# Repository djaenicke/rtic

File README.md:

<p align="center">
  <h1 align="center">RTIC</h1>
</p>

### The Hardware
The Real Time Interface and Controller (RTIC) is a universal board for low-level robotics control and monitoring. The board can be ordered from [JLCPCB](https://jlcpcb.com/) using the [assembly](pcb/kicad/v2/assembly) and [gerber](pcb/kicad/v2/gerber) files.

#### Key Features
- 4 permanent magnet DC motor outputs
- 4 quadrature encoder inputs
- 6-axis IMU
- NRF24L01 socket for wireless communications
- USB (supports DFU via jumper)
- CAN breakout header

A [compatible 4-wheeled mobile robot base](https://www.amazon.com/Moebius-Mecanum-Platform-Omni-direactional-Raspberry/dp/B083XS2SD7) can be purchased directly from Amazon. :robot:

### Tools Setup ✔️
At a minium you will need the ARM GNU GCC Toolchain, Make and CMake to compile the source and generate executable artifacts.
-   [ARM GNU GCC Toolchain - 10-2020-q4-major](https://developer.arm.com/tools-and-software/open-source-software/developer-tools/gnu-toolchain/gnu-rm/downloads) - Other versions can be used but the current source is actively developed and tested using the 10-2020-q4-major release
-   Make -  Make is shipped with Linux and should already be present on the developers system. If the developer is running Windows they can either use WSL to run a Linux instance or install Make on Windows via [MinGW](https://sourceforge.net/projects/mingw/)
-   [CMake](https://cmake.org/download/)

To flash and debug the target this project uses a couple of different tools. PyOCD, Segger JLink, or STLINK can be used as the programming/debugging medium, and a VScode extension called Cortex-Debug gives a user interface within VScode for stepping through the source, settings breakpoints and viewing registers/variables within the target.
-   [PyOCD](https://github.com/pyocd/pyOCD#installing)
-   [JLink](https://www.segger.com/downloads/jlink/)
-   [STLINK](https://github.com/stlink-org/stlink)
-   [VScode](https://code.visualstudio.com/)
-   [ARM Developer Extension Pack for VScode](https://marketplace.visualstudio.com/items?itemName=Glasslabs.arm-developer-toolkit)

As an alternative to the debuggging tools, dfu-util can be used to program the board using the built in DFU capability of the bootloader.
-   [dfu-util](https://manpages.ubuntu.com/manpages/xenial/man1/dfu-util.1.html)
    - Linux - ```sudo apt-get install dfu-util```

***NOTE: After installing your desired debug toolset, please ensure the chosen application is accessible from the command line (pyocd or JLinkExe)***

To format all source files, you will need to install Clang-Format.
-   [Clang-Format](https://clang.llvm.org/docs/ClangFormat.html)
    - Linux - ```sudo apt-get install clang-format```

### Compiling, Flashing & Testing ✨
After a fresh clone, the ```setup``` scripts can be used to initialize the project. Passing ```release``` as an argument will generate a release build. Otherwise a ```debug``` build is generated.
##### Windows
```console
setup.ps1
```
##### Linux
```console
./setup.sh
```

Once a project has been initialized, the following commands should be ran from the ```build/``` folder

To clean the working directory:
```console
make clean
```

To compile the source:
```console
make -j8
```

To erase the connected target with PyOCD or Segger JLink:
```console
make erase
```

To flash the connected target with PyOCD or Segger JLink:
```console
make flash
```

To flash the connected target via DFU:
```console
make dfu
```

To execute unit tests:
```console
make test
```

To format source files:
```console
make format
```

### Source Documentation Style 📃
Read more about the Source documentation style [here](./doc/DOCUMENTATION_STYLE.md)

### Develop Strategy 📖
Read more about the Git develop strategy used [here](./doc/DEVELOP_STRATEGY.md)

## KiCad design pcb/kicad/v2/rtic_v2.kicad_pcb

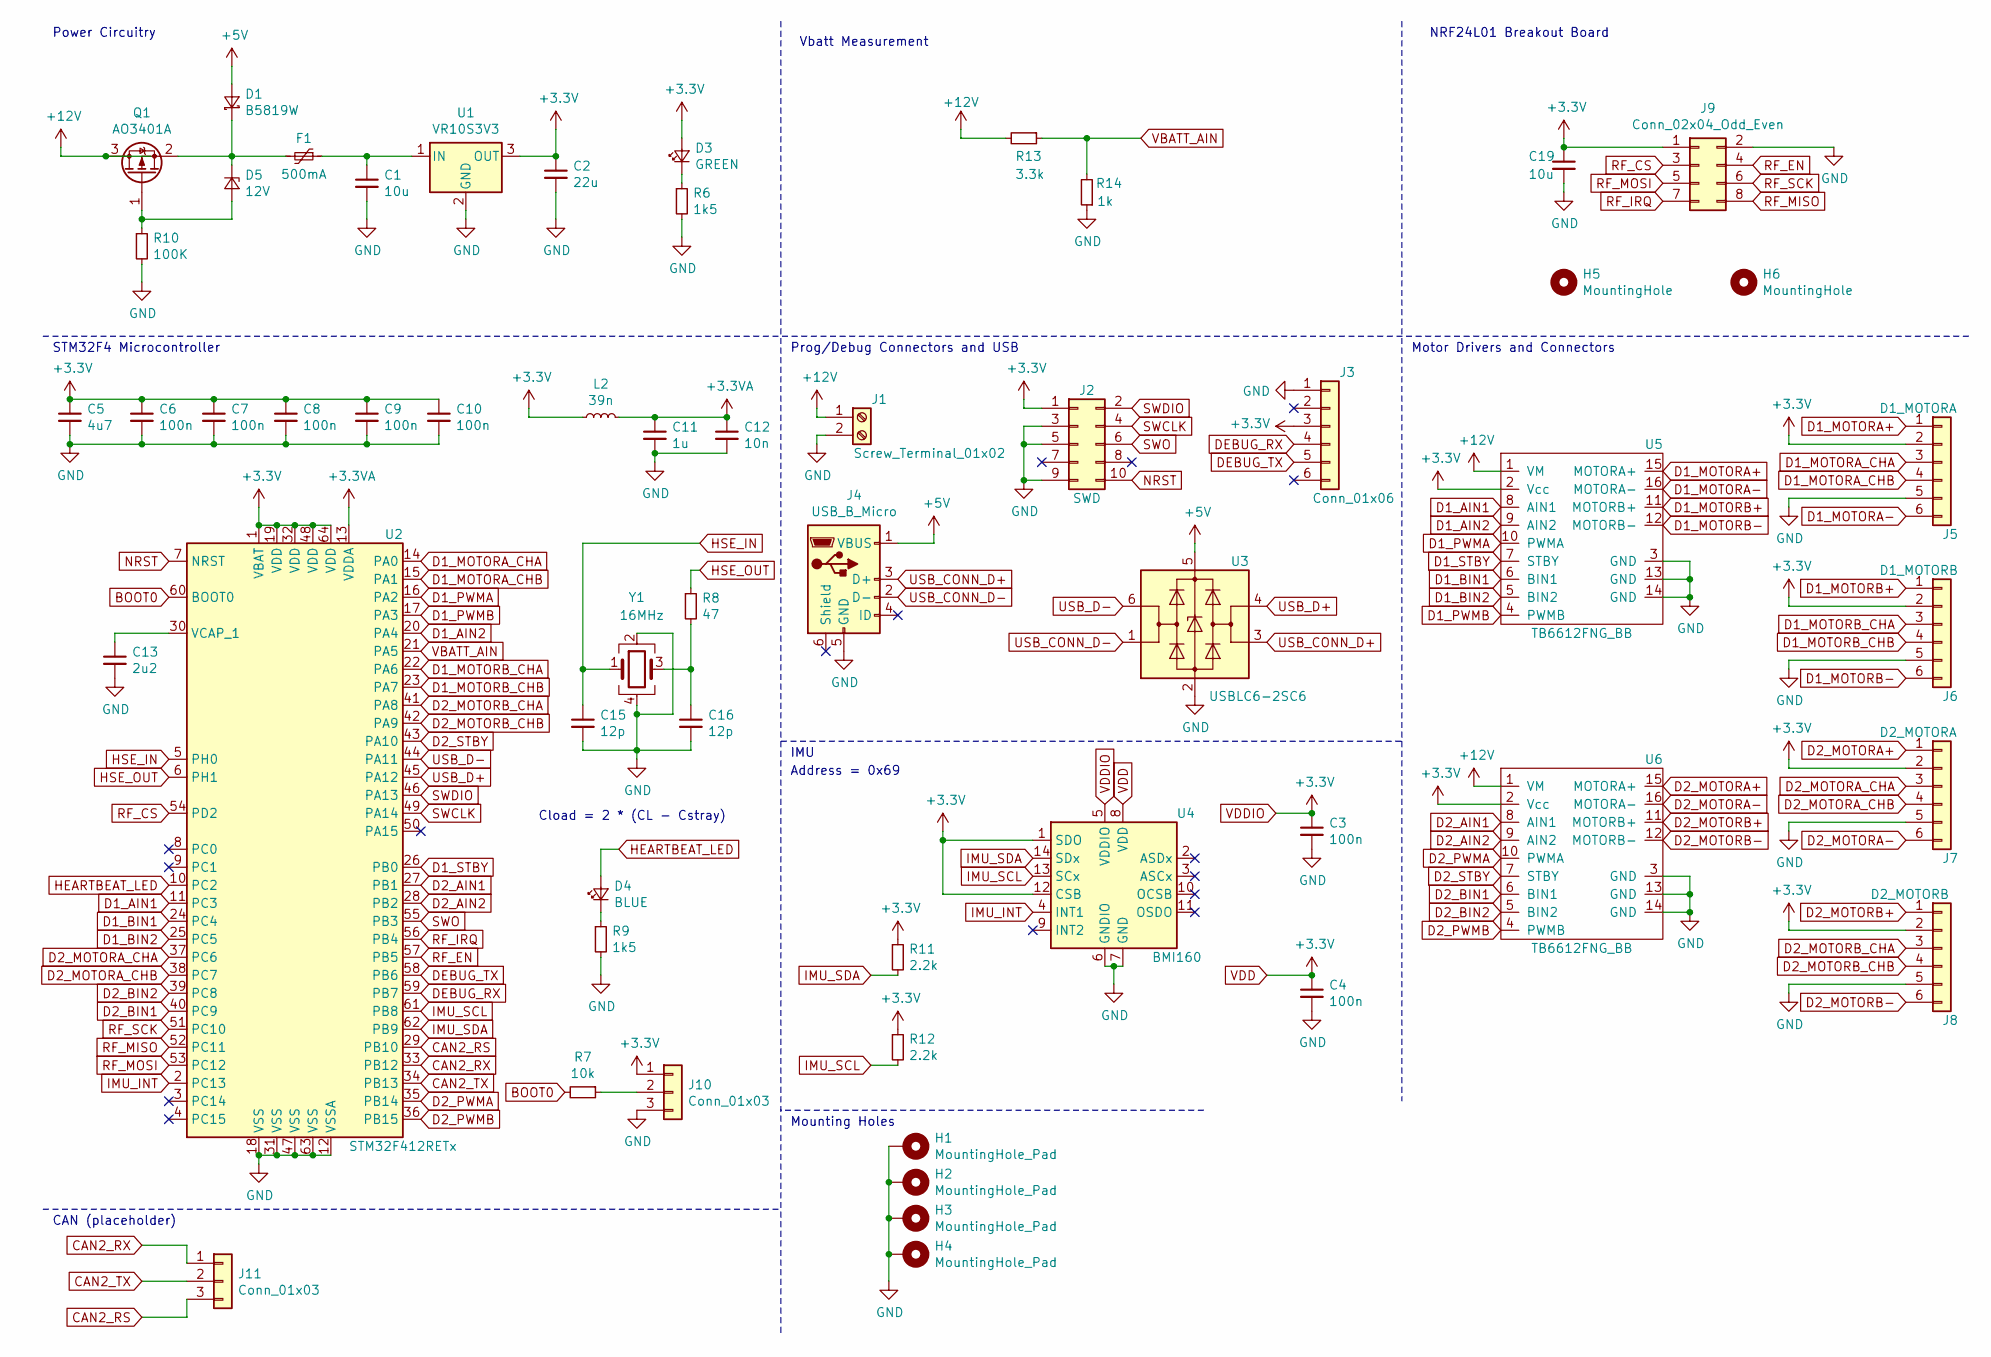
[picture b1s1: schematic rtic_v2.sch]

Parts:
C1, C19: 10u; C_1206_3216Metric; LCSC Part # C13585
C2: 22u; C_1206_3216Metric; LCSC Part # C12891
C3, C4, C6, C7, C8, C9, C10: 100n; C_0402_1005Metric; LCSC Part # C1525
C5: 4u7; C_0603_1608Metric; LCSC Part # C19666
C11: 1u; C_0603_1608Metric; LCSC Part # C15849
C12: 10n; C_0402_1005Metric; LCSC Part # C15195
C13: 2u2; C_0603_1608Metric; LCSC Part # C23630
C15, C16: 12p; C_0402_1005Metric; LCSC Part # C1547
D1: B5819W; D_SOD-123; LCSC Part # C8598
D3: GREEN; LED_0603_1608Metric; LCSC Part # C72043
D4: BLUE; LED_0603_1608Metric; LCSC Part # C72041
D5: 12V; D_SOD-323; LCSC Part # C261261
F1: 500mA; Fuse_1206_3216Metric; LCSC Part # C99561
H1, H2, H3, H4: MountingHole_Pad; MountingHole_3.2mm_M3_Pad_Via
H5, H6: MountingHole; MountingHole_2.7mm_M2.5
J1: Screw_Terminal_01x02; TerminalBlock_Phoenix_PT-1,5-2-5.0-H_1x02_P5.00mm_Horizontal
J2: SWD; PinHeader_2x05_P1.27mm_Vertical_SMD
J3: Conn_01x06; PinHeader_1x06_P2.54mm_Vertical
J4: USB_B_Micro; USB_Micro-B_Amphenol_10103594-0001LF_Horizontal
J5: D1_MOTORA; JST_PH_B6B-PH-K_1x06_P2.00mm_Vertical
J6: D1_MOTORB; JST_PH_B6B-PH-K_1x06_P2.00mm_Vertical
J7: D2_MOTORA; JST_PH_B6B-PH-K_1x06_P2.00mm_Vertical
J8: D2_MOTORB; JST_PH_B6B-PH-K_1x06_P2.00mm_Vertical
J9: Conn_02x04_Odd_Even; PinSocket_2x04_P2.54mm_Vertical
J10, J11: Conn_01x03; PinHeader_1x03_P2.54mm_Vertical
L2: 39n; L_0402_1005Metric; LCSC Part # C26443
Q1: AO3401A; SOT-23; LCSC Part # C15127
R6, R9: 1k5; R_0603_1608Metric; LCSC Part # C22843
R7: 10k; R_0402_1005Metric; LCSC Part # C25744
R8: 47; R_0402_1005Metric; LCSC Part # C25118
R10: 100K; R_0603_1608Metric; LCSC Part # C25803
R11, R12: 2.2k; R_0402_1005Metric; LCSC Part # C25879
R13: 3.3k; R_0402_1005Metric; LCSC Part # C25890
R14: 1k; R_0402_1005Metric; LCSC Part # C11702
U1: VR10S3V3
U2: STM32F412RETx; LQFP-64_10x10mm_P0.5mm; LCSC Part # C89374
U3: USBLC6-2SC6; SOT-23-6; LCSC Part # C7519
U4: BMI160; Bosch_LGA-14_3x2.5mm_P0.5mm; LCSC Part # C94021
U5, U6: TB6612FNG_BB
Y1: 16MHz; Crystal_SMD_3225-4Pin_3.2x2.5mm; LCSC Part # C13738

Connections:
+3.3VA: C11.1, C12.1, L2.2, U2.13 (VDDA)
+5V: D1.2 (A), J4.1 (VBUS), U3.5 (VBUS)
+12V: J1.1, Q1.3 (D), R13.2, U5.1 (VM), U6.1 (VM)
BOOT0: R7.2, U2.60 (BOOT0)
CAN2_RS: J11.3, U2.29 (PB10)
CAN2_RX: J11.1, U2.33 (PB12)
CAN2_TX: J11.2, U2.34 (PB13)
D1_AIN1: U2.11 (PC3), U5.8 (AIN1)
D1_AIN2: U2.20 (PA4), U5.9 (AIN2)
D1_BIN1: U2.24 (PC4), U5.6 (BIN1)
D1_BIN2: U2.25 (PC5), U5.5 (BIN2)
D1_MOTORA+: J5.1, U5.15 (MOTORA+)
D1_MOTORA-: J5.6, U5.16 (MOTORA-)
D1_MOTORA_CHA: J5.3, U2.14 (PA0)
D1_MOTORA_CHB: J5.4, U2.15 (PA1)
D1_MOTORB+: J6.1, U5.11 (MOTORB+)
D1_MOTORB-: J6.6, U5.12 (MOTORB-)
D1_MOTORB_CHA: J6.3, U2.22 (PA6)
D1_MOTORB_CHB: J6.4, U2.23 (PA7)
D1_PWMA: U2.16 (PA2), U5.10 (PWMA)
D1_PWMB: U2.17 (PA3), U5.4 (PWMB)
D1_STBY: U2.26 (PB0), U5.7 (STBY)
D2_AIN1: U2.27 (PB1), U6.8 (AIN1)
D2_AIN2: U2.28 (PB2), U6.9 (AIN2)
D2_BIN1: U2.40 (PC9), U6.6 (BIN1)
D2_BIN2: U2.39 (PC8), U6.5 (BIN2)
D2_MOTORA+: J7.1, U6.15 (MOTORA+)
D2_MOTORA-: J7.6, U6.16 (MOTORA-)
D2_MOTORA_CHA: J7.3, U2.37 (PC6)
D2_MOTORA_CHB: J7.4, U2.38 (PC7)
D2_MOTORB+: J8.1, U6.11 (MOTORB+)
D2_MOTORB-: J8.6, U6.12 (MOTORB-)
D2_MOTORB_CHA: J8.3, U2.41 (PA8)
D2_MOTORB_CHB: J8.4, U2.42 (PA9)
D2_PWMA: U2.35 (PB14), U6.10 (PWMA)
D2_PWMB: U2.36 (PB15), U6.4 (PWMB)
D2_STBY: U2.43 (PA10), U6.7 (STBY)
DEBUG_RX: J3.4, U2.59 (PB7)
DEBUG_TX: J3.5, U2.58 (PB6)
GND: C1.2, C2.2, C3.2, C4.2, C5.2, C6.2, C7.2, C8.2, C9.2, C10.2, C11.2, C12.2, C13.2, C15.2, C16.2, C19.2, H1.1, H2.1, H3.1, H4.1, J1.2, J2.3, J2.5, J2.9, J3.1, J4.5 (GND), J5.5, J6.5, J7.5, J8.5, J9.2, J10.3, R6.2, R9.2, R10.2, R14.1, U1.2 (GND), U2.12 (VSSA), U2.18 (VSS), U2.31 (VSS), U2.47 (VSS), U2.63 (VSS), U3.2 (GND), U4.6 (GNDIO), U4.7 (GND), U5.3 (GND), U5.13 (GND), U5.14 (GND), U6.3 (GND), U6.13 (GND), U6.14 (GND), Y1.2, Y1.4
HEARTBEAT_LED: D4.2 (A), U2.10 (PC2)
HSE_IN: C15.1, U2.5 (PH0), Y1.1
HSE_OUT: R8.1, U2.6 (PH1)
IMU_INT: U2.2 (PC13), U4.4 (INT1)
IMU_SCL: R12.2, U2.61 (PB8), U4.13 (SCx)
IMU_SDA: R11.2, U2.62 (PB9), U4.14 (SDx)
NRST: J2.10, U2.7 (NRST)
unnamed: C1.1, F1.1, U1.1 (IN)
unnamed: C13.1, U2.30 (VCAP_1)
unnamed: C16.1, R8.2, Y1.3
unnamed: D1.1 (K), D5.1 (K), F1.2, Q1.2 (S)
unnamed: D3.1 (K), R6.1
unnamed: D4.1 (K), R9.1
unnamed: D5.2 (A), Q1.1 (G), R10.1
unnamed: J10.2, R7.1
RF_CS: J9.3, U2.54 (PD2)
RF_EN: J9.4, U2.57 (PB5)
RF_IRQ: J9.7, U2.56 (PB4)
RF_MISO: J9.8, U2.52 (PC11)
RF_MOSI: J9.5, U2.53 (PC12)
RF_SCK: J9.6, U2.51 (PC10)
SWCLK: J2.4, U2.49 (PA14)
SWDIO: J2.2, U2.46 (PA13)
SWO: J2.6, U2.55 (PB3)
USB_CONN_D+: J4.3 (D+), U3.3 (I/O2)
USB_CONN_D-: J4.2 (D-), U3.1 (I/O1)
USB_D+: U2.45 (PA12), U3.4 (I/O2)
USB_D-: U2.44 (PA11), U3.6 (I/O1)
VBATT_AIN: R13.1, R14.2, U2.21 (PA5)
VDD: C2.1, C3.1, C4.1, C5.1, C6.1, C7.1, C8.1, C9.1, C10.1, C19.1, D3.2 (A), J2.1, J3.3, J5.2, J6.2, J7.2, J8.2, J9.1, J10.1, L2.1, R11.1, R12.1, U1.3 (OUT), U2.1 (VBAT), U2.19 (VDD), U2.32 (VDD), U2.48 (VDD), U2.64 (VDD), U4.1 (SDO), U4.5 (VDDIO), U4.8 (VDD), U4.12 (CSB), U5.2 (Vcc), U6.2 (Vcc)

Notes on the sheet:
Cload = 2 * (CL - Cstray)
STM32F4 Microcontroller
Power Circuitry
Prog/Debug Connectors and USB
IMU
Mounting Holes
Motor Drivers and Connectors
NRF24L01 Breakout Board
CAN (placeholder)
Vbatt Measurement
Address = 0x69

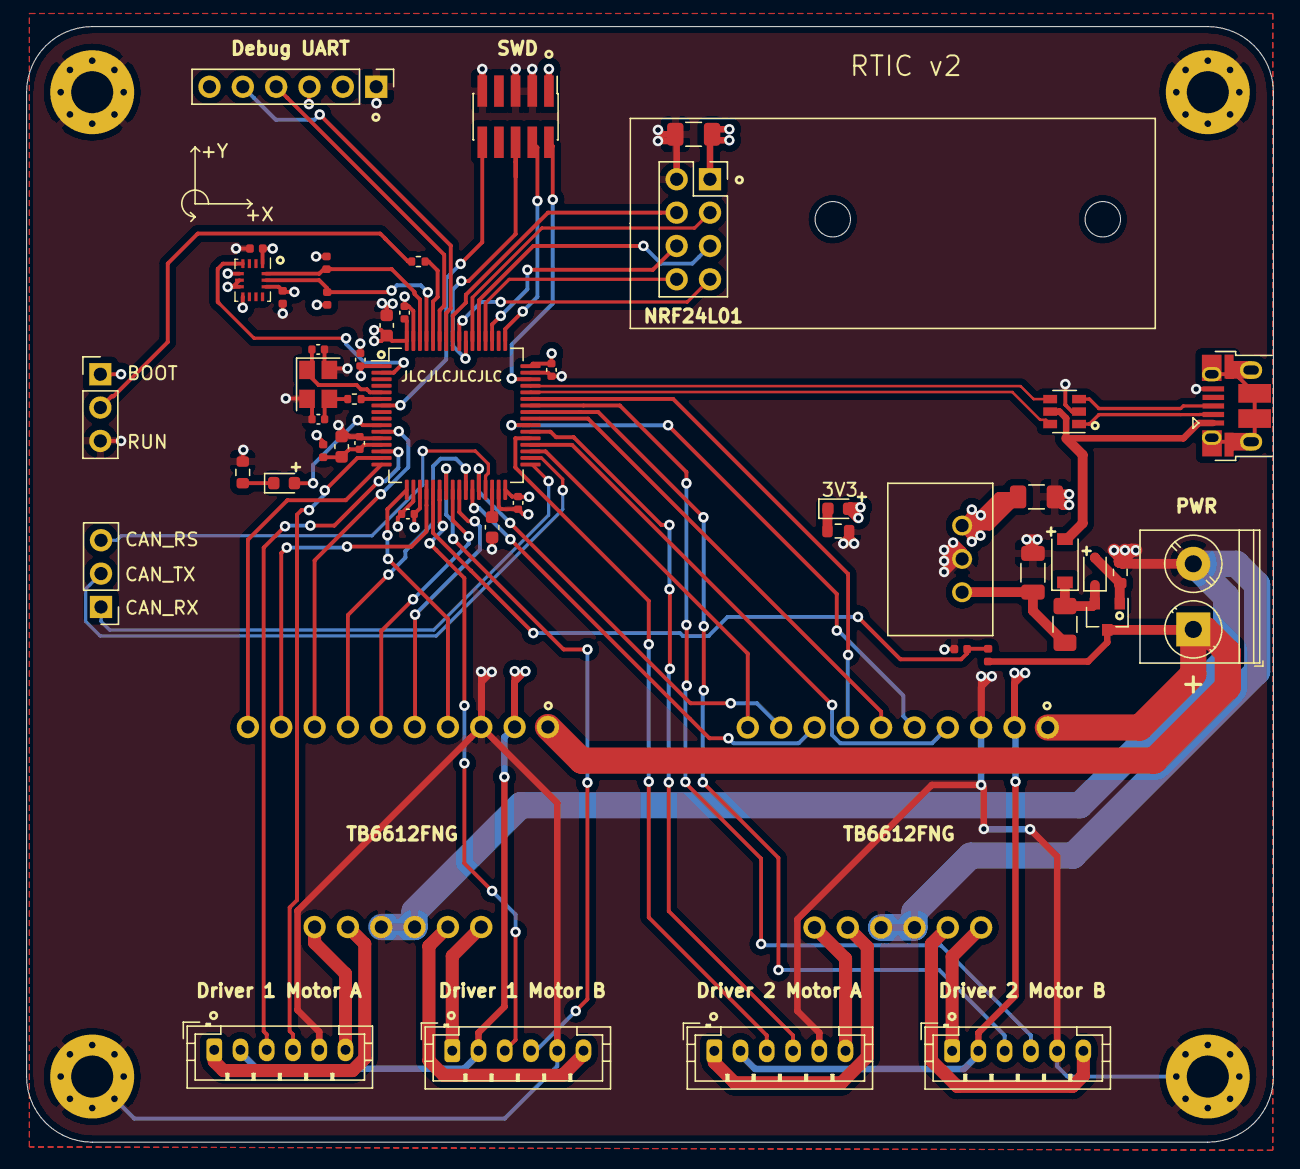
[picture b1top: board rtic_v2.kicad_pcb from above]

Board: 4 copper layers, 95.0 x 85.0 mm, 56 parts (0 on the bottom side), 70 nets.

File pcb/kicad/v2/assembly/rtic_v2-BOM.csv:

Comment,Designator,Footprint,LCSC
"10u","C1,C19","Capacitor_SMD:C_1206_3216Metric","C13585"
"1u","C11","Capacitor_SMD:C_0603_1608Metric","C15849"
"10n","C12","Capacitor_SMD:C_0402_1005Metric","C15195"
"2u2","C13","Capacitor_SMD:C_0603_1608Metric","C23630"
"12p","C15,C16","Capacitor_SMD:C_0402_1005Metric","C1547"
"22u","C2","Capacitor_SMD:C_1206_3216Metric","C12891"
"4u7","C5","Capacitor_SMD:C_0603_1608Metric","C19666"
"100n","C3,C4,C6,C7,C8,C9,C10","Capacitor_SMD:C_0402_1005Metric","C1525"
"B5819W","D1","Diode_SMD:D_SOD-123","C8598"
"GREEN","D3","LED_SMD:LED_0603_1608Metric","C72043"
"BLUE","D4","LED_SMD:LED_0603_1608Metric","C72041"
"12V","D5","Diode_SMD:D_SOD-323","C261261"
"500mA","F1","Fuse:Fuse_1206_3216Metric","C99561"
"MountingHole_Pad","H1,H2,H3,H4","MountingHole:MountingHole_3.2mm_M3_Pad_Via",""
"MountingHole","H5,H6","MountingHole:MountingHole_2.7mm_M2.5",""
"Screw_Terminal_01x02","J1","TerminalBlock_Phoenix:TerminalBlock_Phoenix_PT-1,5-2-5.0-H_1x02_P5.00mm_Horizontal",""
"Conn_01x03","J10,J11","Connector_PinHeader_2.54mm:PinHeader_1x03_P2.54mm_Vertical",""
"SWD","J2","Connector_PinHeader_1.27mm:PinHeader_2x05_P1.27mm_Vertical_SMD",""
"Conn_01x06","J3","Connector_PinHeader_2.54mm:PinHeader_1x06_P2.54mm_Vertical",""
"USB_B_Micro","J4","Connector_USB:USB_Micro-B_Amphenol_10103594-0001LF_Horizontal",""
"D1_MOTORA","J5","Connector_JST:JST_PH_B6B-PH-K_1x06_P2.00mm_Vertical",""
"D1_MOTORB","J6","Connector_JST:JST_PH_B6B-PH-K_1x06_P2.00mm_Vertical",""
"D2_MOTORA","J7","Connector_JST:JST_PH_B6B-PH-K_1x06_P2.00mm_Vertical",""
"D2_MOTORB","J8","Connector_JST:JST_PH_B6B-PH-K_1x06_P2.00mm_Vertical",""
"Conn_02x04_Odd_Even","J9","Connector_PinSocket_2.54mm:PinSocket_2x04_P2.54mm_Vertical",""
"39n","L2","Inductor_SMD:L_0402_1005Metric","C26443"
"AO3401A","Q1","Package_TO_SOT_SMD:SOT-23","C15127"
"100K","R10","Resistor_SMD:R_0603_1608Metric","C25803"
"2.2k","R11,R12","Resistor_SMD:R_0402_1005Metric","C25879"
"3.3k","R13","Resistor_SMD:R_0402_1005Metric","C25890"
"1k","R14","Resistor_SMD:R_0402_1005Metric","C11702"
"10k","R7","Resistor_SMD:R_0402_1005Metric","C25744"
"47","R8","Resistor_SMD:R_0402_1005Metric","C25118"
"1k5","R6,R9","Resistor_SMD:R_0603_1608Metric","C22843"
"VR10S3V3","U1","dj:VR10S3V3",""
"STM32F412RETx","U2","Package_QFP:LQFP-64_10x10mm_P0.5mm","C89374"
"USBLC6-2SC6","U3","Package_TO_SOT_SMD:SOT-23-6","C7519"
"BMI160","U4","Package_LGA:Bosch_LGA-14_3x2.5mm_P0.5mm","C94021"
"TB6612FNG_BB","U5,U6","dj:TB6612FNG_BB",""
"16MHz","Y1","Crystal:Crystal_SMD_3225-4Pin_3.2x2.5mm","C13738"

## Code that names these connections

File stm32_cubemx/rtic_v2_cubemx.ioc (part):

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Mcu.Name=STM32F412R(E-G)Tx
Mcu.Package=LQFP64
Mcu.UserName=STM32F412RETx
PA0.GPIOParameters=GPIO_Label
PA0.GPIO_Label=D1_MOTORA_CHA
PA0.Signal=S_TIM5_CH1
PA1.GPIOParameters=GPIO_Label
PA1.GPIO_Label=D1_MOTORA_CHB
PA1.Signal=S_TIM5_CH2
PA10.GPIOParameters=GPIO_Label
PA10.GPIO_Label=D2_STBY
PA10.Signal=GPIO_Output
PA11.Mode=Device_Only
PA11.Signal=USB_OTG_FS_DM
PA12.Mode=Device_Only
PA12.Signal=USB_OTG_FS_DP
PA13.Signal=SYS_JTMS-SWDIO
PA14.Signal=SYS_JTCK-SWCLK
PA2.GPIOParameters=GPIO_Label
PA2.GPIO_Label=D1_PWMA
PA2.Signal=S_TIM9_CH1
PA3.GPIOParameters=GPIO_Label
PA3.GPIO_Label=D1_PWMB
PA3.Signal=S_TIM9_CH2
PA4.GPIOParameters=GPIO_Label
PA4.GPIO_Label=D1_AIN2
PA4.Signal=GPIO_Output
PA5.GPIOParameters=GPIO_Label
PA5.GPIO_Label=VBATT_AIN
PA5.Signal=ADCx_IN5
PA6.GPIOParameters=GPIO_Label
PA6.GPIO_Label=D1_MOTORB_CHA
PA6.Signal=S_TIM3_CH1
PA7.GPIOParameters=GPIO_Label
PA7.GPIO_Label=D1_MOTORB_CHB
PA7.Signal=S_TIM3_CH2
PA8.GPIOParameters=GPIO_Label,GPIO_ModeDefaultEXTI
PA8.GPIO_Label=D2_MOTORB_CHA
PA8.GPIO_ModeDefaultEXTI=GPIO_MODE_IT_RISING_FALLING
PA8.Signal=GPXTI8
PA9.GPIOParameters=GPIO_Label,GPIO_ModeDefaultEXTI
PA9.GPIO_Label=D2_MOTORB_CHB
PA9.GPIO_ModeDefaultEXTI=GPIO_MODE_IT_RISING_FALLING
PA9.Signal=GPXTI9
PB0.GPIOParameters=GPIO_Label
PB0.GPIO_Label=D1_STBY
PB0.Signal=GPIO_Output
PB1.GPIOParameters=GPIO_Label
PB1.GPIO_Label=D2_AIN1
PB1.Signal=GPIO_Output
PB10.GPIOParameters=GPIO_Label
PB10.GPIO_Label=CAN2_RS
PB10.Signal=GPIO_Output
PB12.Mode=CAN_Activate
PB12.Signal=CAN2_RX
PB13.Mode=CAN_Activate
PB13.Signal=CAN2_TX
PB14.GPIOParameters=GPIO_Label
PB14.GPIO_Label=D2_PWMA
PB14.Signal=S_TIM12_CH1
PB15.GPIOParameters=GPIO_Label
PB15.GPIO_Label=D2_PWMB
PB15.Signal=S_TIM12_CH2
PB2.GPIOParameters=GPIO_Label
PB2.GPIO_Label=D2_AIN2
PB2.Signal=GPIO_Output
PB3.Signal=SYS_JTDO-SWO
PB4.GPIOParameters=GPIO_Label
PB4.GPIO_Label=RF_IRQ
PB4.Signal=GPIO_Input
PB5.GPIOParameters=GPIO_Label
PB5.GPIO_Label=RF_EN
PB5.Signal=GPIO_Output
PB6.GPIOParameters=GPIO_Label
PB6.GPIO_Label=DEBUG_TX
PB6.Mode=Asynchronous
PB6.Signal=USART1_TX
PB7.GPIOParameters=GPIO_Label
PB7.GPIO_Label=DEBUG_RX
PB7.Mode=Asynchronous
PB7.Signal=USART1_RX
PB8.GPIOParameters=GPIO_Label
PB8.GPIO_Label=IMU_SCL
PB8.Mode=I2C
PB8.Signal=I2C1_SCL
PB9.GPIOParameters=GPIO_Label
PB9.GPIO_Label=IMU_SDA
PB9.Mode=I2C
PB9.Signal=I2C1_SDA
PC10.GPIOParameters=GPIO_Label
PC10.GPIO_Label=RF_SCK
PC10.Mode=Full_Duplex_Master
PC10.Signal=SPI3_SCK
PC11.GPIOParameters=GPIO_Label
PC11.GPIO_Label=RF_MISO
PC11.Mode=Full_Duplex_Master
PC11.Signal=SPI3_MISO
PC12.GPIOParameters=GPIO_Label
PC12.GPIO_Label=RF_MOSI
PC12.Mode=Full_Duplex_Master
PC12.Signal=SPI3_MOSI
PC13.GPIOParameters=GPIO_Label
PC13.GPIO_Label=IMU_INT
PC13.Signal=GPIO_Input
PC14-OSC32_IN.Mode=LSE-External-Oscillator
PC14-OSC32_IN.Signal=RCC_OSC32_IN
PC15-OSC32_OUT.Mode=LSE-External-Oscillator
PC15-OSC32_OUT.Signal=RCC_OSC32_OUT
PC2.GPIOParameters=GPIO_Label
PC2.GPIO_Label=HEARTBEAT_LED
PC2.Signal=GPIO_Output
PC3.GPIOParameters=GPIO_Label
PC3.GPIO_Label=D1_AIN1
PC3.Signal=GPIO_Output
PC4.GPIOParameters=GPIO_Label
PC4.GPIO_Label=D1_BIN1
PC4.Signal=GPIO_Output
PC5.GPIOParameters=GPIO_Label
PC5.GPIO_Label=D1_BIN2
PC5.Signal=GPIO_Output
PC6.GPIOParameters=GPIO_Label,GPIO_ModeDefaultEXTI
PC6.GPIO_Label=D2_MOTORA_CHA
PC6.GPIO_ModeDefaultEXTI=GPIO_MODE_IT_RISING_FALLING
PC6.Signal=GPXTI6
PC7.GPIOParameters=GPIO_Label,GPIO_ModeDefaultEXTI
PC7.GPIO_Label=D2_MOTORA_CHB
PC7.GPIO_ModeDefaultEXTI=GPIO_MODE_IT_RISING_FALLING
PC7.Signal=GPXTI7
PC8.GPIOParameters=GPIO_Label
PC8.GPIO_Label=D2_BIN2
PC8.Signal=GPIO_Output
PC9.GPIOParameters=GPIO_Label
PC9.GPIO_Label=D2_BIN1
PC9.Signal=GPIO_Output
PD2.GPIOParameters=GPIO_Label
PD2.GPIO_Label=RF_CS
PD2.Signal=GPIO_Output
PH0\ -\ OSC_IN.GPIOParameters=GPIO_Label
PH0\ -\ OSC_IN.GPIO_Label=HSE_IN
PH0\ -\ OSC_IN.Mode=HSE-External-Oscillator
PH0\ -\ OSC_IN.Signal=RCC_OSC_IN
PH1\ -\ OSC_OUT.GPIOParameters=GPIO_Label
PH1\ -\ OSC_OUT.GPIO_Label=HSE_OUT
PH1\ -\ OSC_OUT.Mode=HSE-External-Oscillator
PH1\ -\ OSC_OUT.Signal=RCC_OSC_OUT
RCC.HSE_VALUE=16000000
RCC.SYSCLKFreq_VALUE=16000000
RCC.SYSCLKSource=RCC_SYSCLKSOURCE_HSE
board=custom

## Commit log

2022-04-02 added STM32F4xx HAL and set project specific CMake variables
2022-04-02 removed readme checklist
2022-04-02 moved firmware into separate directory
2022-04-03 initial implementation of board.c
2022-04-03 added format and dfu make targets
2022-04-03 fixed ci build
2022-04-03 moved doc directory to root and moved .clang-format into firmware directory
2022-04-03 added kicad, assembly, and gerber files
2022-04-03 added cubemx ioc for v2 pcb
2022-04-17 added the ability to use C++
2022-04-17 added GPIO class
2022-04-17 added DigitalIn and DigitalOut classes
2022-04-17 moved initBoard call into startup code
2022-04-17 updated heartbeat LED to use DigitalOut class
2022-04-17 added HwTimer class to enable PWM and quadrature encoders functionality
2022-04-17 updated system clock source to HSE
2022-04-17 added PWM class
2022-04-17 added TB6612 class and tested on all 4 motors
2022-04-17 added QuadratureEncoder class and fixed UART
2022-04-17 updated rear encoders to use interrupts in stm32 cubemx configuration
2022-04-17 updated clang-format to limit line length to 100
2022-04-17 bumped minor version to 2
2022-04-21 split TB6612 class into MotorDriver to separate the two outputs
2022-04-23 initial version of serial_logger
2022-04-23 added FreeRTOS source
2022-04-23 created initial threads
2022-04-23 added the ability to use sprintf with floats
2022-04-24 added VoltageMonitor class
2022-04-24 removed separate directory for tb6612
2022-04-24 motor controllers working in open loop
2022-07-01 added closed loop control capability
2022-07-01 added STLINK debugging capability via vscode
2022-07-01 Revert "Motor controls"
2022-07-01 bumped minor version to 3
2022-07-02 formatting fixes
2022-07-02 added I2C driver and verified the BMI160 interface
2022-07-02 added BMI160 driver
2022-07-02 working version of bmi160 class
2022-07-03 added asserts
2022-07-03 added proper callbacks to IMU class
2022-07-03 added nrf24 driver
2022-07-03 updated method names to camel case
2022-07-03 working version of rf_interface
2022-07-04 reorganized directory structure
2022-07-04 added manual tank drive capability over the RF interface
2022-09-10 bumped minor version to 4
